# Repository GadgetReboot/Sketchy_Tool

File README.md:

# Sketchy Tool
Help tweak a sketch without having to re-program so frequently<br><br>
<br><br>
Send configurable data over I2C to another project so it can tweak parameters on the fly instead of having to re-upload software

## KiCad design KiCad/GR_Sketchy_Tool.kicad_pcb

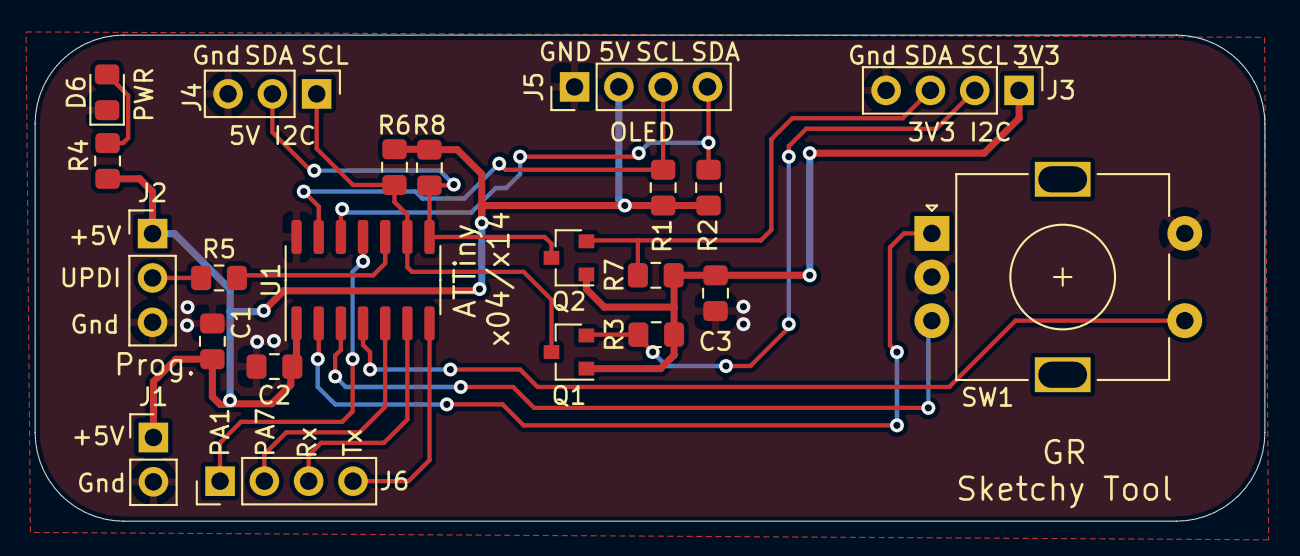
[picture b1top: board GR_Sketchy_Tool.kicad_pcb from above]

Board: 2 copper layers, 70.5 x 27.9 mm, 22 parts (0 on the bottom side), 19 nets.

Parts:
C1: 1uF; C_0805_2012Metric_Pad1.15x1.40mm_HandSolder
C2, C3: 100nF; C_0805_2012Metric_Pad1.15x1.40mm_HandSolder
D6: Power; LED_0805_2012Metric_Pad1.15x1.40mm_HandSolder
J1: Conn_01x02; PinHeader_1x02_P2.54mm_Vertical
J2, J4: Conn_01x03; PinHeader_1x03_P2.54mm_Vertical
J3, J5, J6: Conn_01x04; PinHeader_1x04_P2.54mm_Vertical
Q1, Q2: BSS138; SOT-23
R1, R2, R3, R6, R7, R8: 10K; R_0805_2012Metric_Pad1.15x1.40mm_HandSolder
R4, R5: 1K; R_0805_2012Metric_Pad1.15x1.40mm_HandSolder
SW1: Rotary_Encoder_Switch; RotaryEncoder_Alps_EC11E-Switch_Vertical_H20mm
U1: ATtiny x04/x14; SOIC-14_3.9x8.7mm_P1.27mm

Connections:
+3V3: C3.1, J3.1, Q1.1, Q2.1, R3.2, R7.2
+5V: C1.1, C2.1, J1.1, J2.1, J5.2, R1.1, R2.1, R4.1, R6.2, R8.2, U1.1
/ENC_A: SW1.A, U1.2
/ENC_B: SW1.B, U1.3
/ENC_SW: SW1.S1, U1.4
/PA1: J6.1, U1.11
/PA7: J6.2, U1.5
/RX_In: J6.3, U1.6
/SCL: J4.1, Q1.3, R6.1, U1.9
/SCL_3V3: J3.2, Q1.2, R3.1
/SCL_OLED: J5.3, R1.2, U1.13
/SDA: J4.2, Q2.3, R8.1, U1.8
/SDA_3V3: J3.3, Q2.2, R7.1
/SDA_OLED: J5.4, R2.2, U1.12
/TX_Out: J6.4, U1.7
/UPDI: R5.2, U1.10
GNDREF: C1.2, C2.2, C3.2, D6.1, J1.2, J2.3, J3.4, J4.3, J5.1, SW1.C, SW1.S2, U1.14
unnamed: D6.2, R4.2
unnamed: J2.2, R5.1
